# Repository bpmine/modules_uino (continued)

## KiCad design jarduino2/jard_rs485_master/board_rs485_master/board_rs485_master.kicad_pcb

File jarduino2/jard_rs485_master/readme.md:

# Maître des OYAsLe maître des OYAs permet de commander une pompe et plusieurs électrovannes pour remplir des OYAs.## OyasLes OYAs sont des sortes de pots en argile enterrés utilisés depuis des millénaires pour distribuer de l'eau à des cultures.On remplit régulièrement ces pots. Grâce à leur porosité, l'eau se diffuse à travers l'OYAs au fur et à mesure où les racines des plantes assèchent la terre à proximité.- Ils évitent les pertes d'eau par évaporation- ne mouillent pas les feuilles des plantes- ne mouille pas le sol en surface- évitent le stress hydrique- permettent de faire des économies d'eau## Description du système de remplissage automatiqueLe but du système de remplissage automatique des OYAs est de pouvoir s'absenter pendant les vacances tout en laissant les OYAs se gérer tous seuls.### Principe de fonctionnementDes cuves récupèrent l'eau de pluie. A partir de ces cuves, un système comportant une pompe et plusieurs électrovannes permet de remplir les OYAs.Le système rempli chaque OYA jusqu'au maximum ou bien selon le programme souhaité. La stratégie de remplissage est entièrement programmable.### CuvesNous avons 4 cuves pour une capacité totale d'environ 1600 L.- Cuve principale de 1000 L- cuve  "Paul" de 100 L (pour gouteurs petits bacs)- cuve "Réduit" de 250 L pour les OYAs- cuve "Barbec" de 250 L pour les OYAsDeux cuves de 250 L alimentent donc nos deux systèmes de remplissage automatique.Les cuves sont communicantes et un système permet de pomper l'eau de la cuve principale vers les autres. Ce système est décrit ici: [Modules Wifi IO](..\jard_wemos)Des modules Wifi permettent donc de piloter le remplissage des cuves.### Réseau/TuyauChaque système OYAs est composé d'un module maître et de plusieurs modules esclaves reliés entre eux par un réseau RS485 et un tuyau 12mm.Le câble réseau comporte une alimentation 12V et les fils A et B du RS485.Le réseau possède deux résistances de terminaison de 120 Ohms aux deux extrémités. Il est également polarisé côté maître par une pull up et une pull down de 220 Ohms (Valeur encore susceptible de bouger).Pour trouver les bonnes valeurs et étant donné la mauvaise qualité de câble utilisé, il faut effectuer des mesures de signal au bout du bus et vérifier que les tensions au repos de A et de B sont conformes à la norme RS485. __NB:__ Le dispositif de la photo ci-dessus contient une résistance de 128 Ohm. On appelle ça un "bouchon" !! (d'où le bouchon de liège...)## Modules électronique de pilotage### Module PompeLe module pompe contient une carte esclave RS485 en configuration "pompe".Connecteurs:- connecteur 4 voies bus RS485 + alim- connecteur pompe- connecteur débitmètreCe module est placé en sortie de cuve pour pomper l'eau et donner une certaine pression dans le tuyau. La pompe est nécessaire pour assurer un débit constant quelque soit le niveau d'eau dans la cuve et quelle que soit la hauteur relative entre la cuve et les différents OYAs.Il faut aussi noter qu'une pression minimale est nécessaire pour ouvrir une électrovanne (voir ces caractéristiques).Le schéma et le pcb de la carte sont ici: [Carte esclave RS485](..\jard_485_slave\board)Plusieurs versions ont été réalisées, compatibles entre-elles. A ce jour le système est composé de façon hétérogène par ces différentes versions.Version | Date | Description-- | -- | --Rev Ax | 2023 | Version initiale avec modules (forme en L)Rev Bx | 2023 | Correction RX/TX inverséRev Dx | 2024 | Version sans module (tout intégré en CMS)Rev Ex | 2024 | Avec modules (petite carte)Rev Gx | 2024 | MAX485 en CMS (petite carte)Le logiciel est ici: [Logiciel esclave RS485](..\jard_485_slave\soft)### Module OyaLe module OYA contient une carte esclave RS485 en configuration "OYA".Connecteurs:- connecteur 4 voies bus RS485 + alim- connecteur électrovanne- connecteur niveauxIl contient également une électrovanne 12V et un capteur de niveau.Ce module est placé sur chaque OYA.Le capteur de niveau comporte deux flotteurs qui ferment un contact en position basse.### Module Maître## Protocole réseau (RS485)### PrincipeLe réseau est de type RS485. Il comporte un maître et plusieurs esclaves. Chaque esclave a une adresse unique (de 1 à 14 ou 1 à E en hexadécimal).Seul le maître peut initier une communication. Un seul esclave peut répondre à une trame émise par le maître.Types de messages du maître:- Trame Commandes- Trame Ping- Trame SyncTypes de réponses d'un esclave:- Trame Pompe- Trame Oya- Trame PongLa communication se fait par cycles. Chaque cycle se termine par une trame Sync.Durant un cycle, le maître envoie autant de trames __*"Commandes"*__ qu'il y'a d'esclaves configurés. Chaque trame __*"Commandes"*__ comporte un appel destiné à un esclave en particulier. Seul l'esclave appelé peut répondre avec l'une des deux trames __*"Oya"*__ ou __*"Pompe"*__.Après un __*"Sync"*__, le maître doit impérativement attendre un temps minimum avant d'initier un nouveau cycle. Cela permet aux esclaves d'effectuer des traitements.#### Echange Commandes##### Trame Commandes##### Trame Pompe##### Trame Oya#### Echange Ping/Pong#### Timing notableTemps de cycleTemps entre le sync et un nouveau cycle

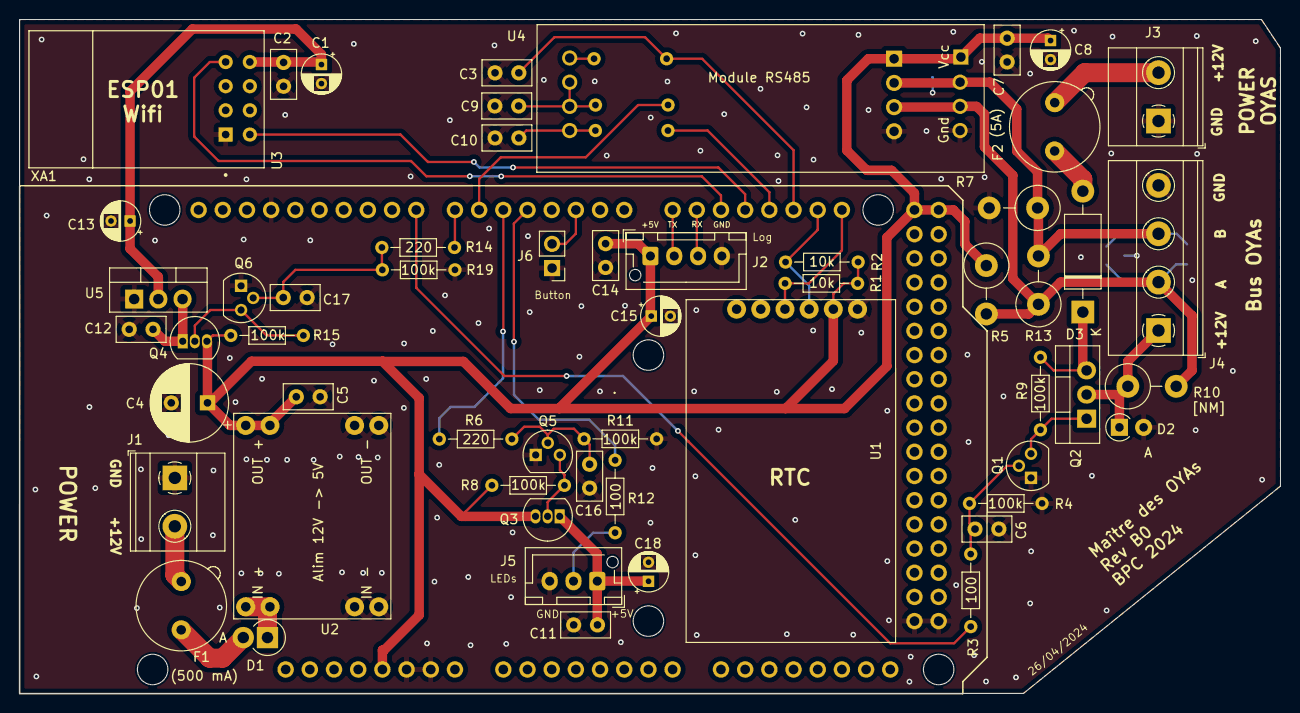
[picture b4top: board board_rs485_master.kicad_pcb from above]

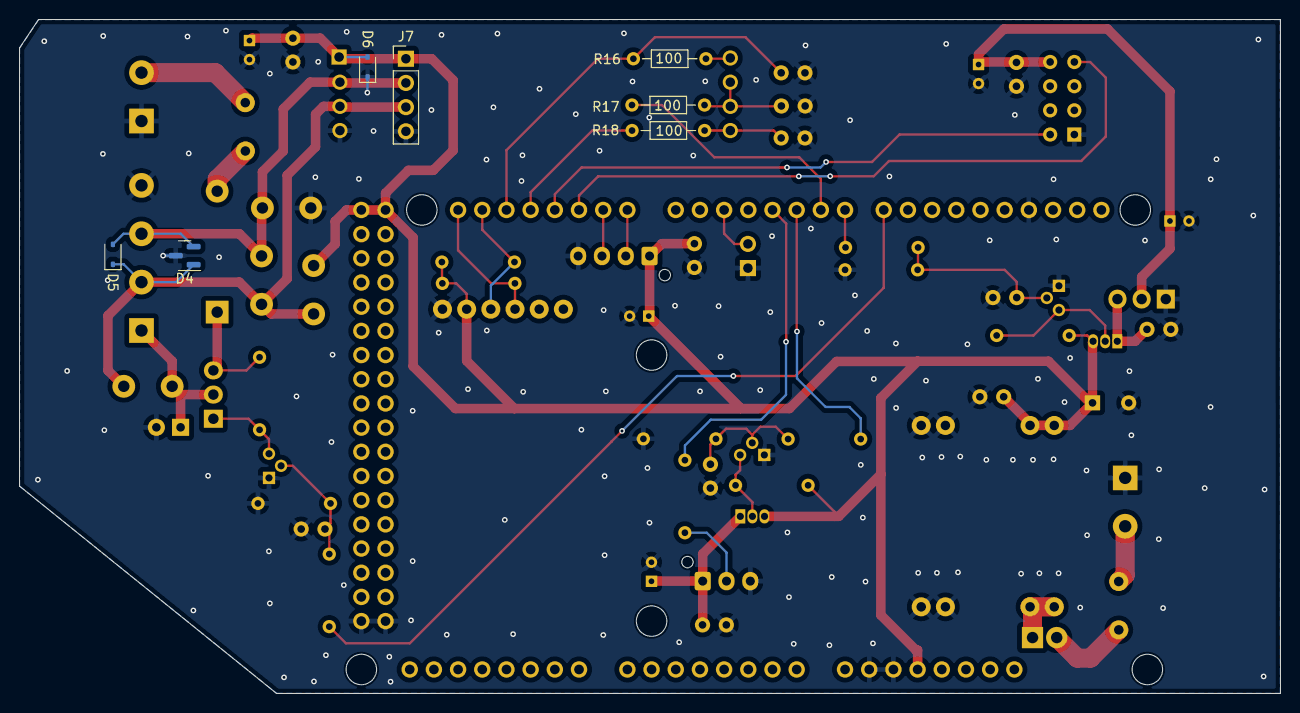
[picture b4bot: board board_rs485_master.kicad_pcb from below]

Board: 2 copper layers, 132.4 x 70.8 mm, 64 parts (7 on the bottom side), 38 nets.

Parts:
C1, C8, C13, C15, C18: 10µF; CP_Radial_D4.0mm_P2.00mm
C2, C5, C6, C7, C11, C12, C14, C16, C17: 100nF; C_Disc_D5.0mm_W2.5mm_P2.50mm
C3, C9, C10: 1nF; C_Disc_D5.0mm_W2.5mm_P2.50mm
C4: 100µF; CP_Radial_D8.0mm_P3.80mm
D1: SR560; D_DO-15_P2.54mm_Vertical_AnodeUp
D2: BAT42; D_A-405_P2.54mm_Vertical_AnodeUp
D3: SR560; D_DO-15_P12.70mm_Horizontal
D4: SM712_SOT23; SOT-23
D5, D6: SD12_SOD323; D_SOD-323
F1: 500 mA; Fuseholder_TR5_Littelfuse_No560_No460
F2: 5A; Fuseholder_TR5_Littelfuse_No560_No460
J1: POWER_12V; TerminalBlock_Phoenix_MKDS-1,5-2-5.08_1x02_P5.08mm_Horizont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
J2: Log; JST_XH_B4B-XH-AM_1x04_P2.50mm_Vertical
J3: POWER_OYAS_12V; TerminalBlock_Phoenix_MKDS-1,5-2-5.08_1x02_P5.08mm_Horizont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
J4: BUS_OYAS; TerminalBlock_Phoenix_MKDS-1,5-4-5.08_1x04_P5.08mm_Horizont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
J5: Leds RGB; JST_XH_B3B-XH-AM_1x03_P2.50mm_Vertical
J6: Button; PinHeader_1x02_P2.54mm_Vertical
J7: Adapt BUS; PinHeader_1x04_P2.54mm_Vertical
Q1, Q5, Q6: BPC_2N2222A; TO-92
Q2: P03P4L-04; TO-220-3_Vertical
Q3, Q4: BC327; TO-92_Inline
R1, R2: 10k; R_Axial_DIN0204_L3.6mm_D1.6mm_P7.62mm_Horizontal
R3, R12, R16, R17, R18: 100; R_Axial_DIN0204_L3.6mm_D1.6mm_P7.62mm_Horizontal
R4, R8, R9, R11, R15, R19: 100k; R_Axial_DIN0204_L3.6mm_D1.6mm_P7.62mm_Horizontal
R5, R7: 220; R_Axial_DIN0414_L11.9mm_D4.5mm_P5.08mm_Vertical
R6, R14: 220; R_Axial_DIN0204_L3.6mm_D1.6mm_P7.62mm_Horizontal
R10: R; R_Axial_DIN0414_L11.9mm_D4.5mm_P5.08mm_Vertical
R13: 128; R_Axial_DIN0414_L11.9mm_D4.5mm_P5.08mm_Vertical
U1: RtcArduino; BPC_RtcArduino
U2: BPC_Alim5V
U3: BPC_ESP8266-01_ESP-01; BPC_XCVR_ESP8266-01_ESP-01
U4: BPC_Mod485
U5: LM1117DT-3.3; TO-220-3_Vertical
XA1: Arduino_Mega2560_Shield; BPC_Arduino_Mega2560_Shield

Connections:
+5V: C4.1, C5.1, C7.1, C8.1, C14.1, C15.1, D6.2 (A2), J2.1, J7.1, Q3.3 (E), Q4.3 (E), R1.1, R2.1, R5.1, R8.1, R15.1, U1.2 (VCC), U2.7 (OUT+), U2.8 (OUT+), U4.1 (Vcc), XA1.5V1 (5V), XA1.5V3 (5V), XA1.5V4 (5V)
A: D4.1 (A1), D5.1 (A1), J4.2, J7.3, R5.2, R10.2, R13.1, U4.3 (A)
B: D4.2 (A2), D5.2 (A2), J4.3, J7.2, R7.1, R13.2, U4.2 (B)
CMD_LEDS_PWR: R6.1, XA1.D5
CMD_OYAS_PWR: R3.2, XA1.D8
CMD_WIFI_PWR: R14.1, XA1.D7
DATA_LEDS: R12.1, XA1.D4
GND: C1.2, C2.2, C3.2, C4.2, C5.2, C6.2, C7.2, C8.2, C9.2, C10.2, C11.2, C12.2, C13.2, C14.2, C15.2, C16.2, C17.2, C18.2, D2.2 (A), D4.3 (common), D6.1 (A1), J1.1, J2.4, J3.1, J4.4, J5.3, J6.1, J7.4, Q1.1, Q5.1, Q6.1, R4.2, R7.2, R11.2, R19.2, U1.1 (GND), U2.3 (IN-), U2.4 (IN-), U2.5 (OUT-), U2.6 (OUT-), U3.1 (GND), U4.4 (Gnd), U5.1 (GND), XA1.GND1 (GND), XA1.GND2 (GND), XA1.GND3 (GND), XA1.GND5 (GND), XA1.GND6 (GND)
unnamed: C6.1, Q1.2, R3.1, R4.1
unnamed: C16.1, Q5.2, R6.2, R11.1
unnamed: C17.1, Q6.2, R14.2, R19.1
unnamed: D1.2 (A), F1.1
unnamed: D1.1 (K), U2.1 (IN+), U2.2 (IN+)
unnamed: D2.1 (K), J4.1, Q2.2 (D), R10.1
unnamed: D3.2 (A), F2.1
unnamed: D3.1 (K), Q2.3 (S), R9.1
unnamed: F1.2, J1.2
unnamed: F2.2, J3.2
unnamed: C11.1, C18.1, J5.1, Q3.1 (C)
unnamed: J5.2, R12.2
unnamed: Q1.3, Q2.1 (G), R9.2
unnamed: Q3.2 (B), Q5.3, R8.2
unnamed: Q4.2 (B), Q6.3, R15.2
unnamed: C12.1, Q4.1 (C), U5.3 (VI)
unnamed: C9.1, R17.1, U4.6 (DE), U4.7 (RE)
unnamed: C10.1, R18.1, U4.5 (DI)
unnamed: R16.1, U4.8 (RO)
POWER_3.3: C1.1, C2.1, C13.1, U3.8 (VCC), U5.2 (VO)
RS485_RX: C3.1, R16.2, XA1.D19 (D19_RX1)
RS485_TX: R18.2, XA1.D18 (D18_TX1)
RX_LOG: J2.3, XA1.D15 (D15_RX3)
RX_WIFI: U3.5 (TXD), XA1.D17 (D17_RX2)
SCL: R1.2, U1.4 (SCL), XA1.D21 (D21_SCL)
SDA: R2.2, U1.3 (SDA), XA1.D20 (D20_SDA)
TEST_BTN: J6.2, XA1.D2 (D2_INT0)
TX_EN: R17.2, XA1.D6
TX_LOG: J2.2, XA1.D14 (D14_TX3)
TX_WIFI: U3.4 (RXD), XA1.D16 (D16_TX2)

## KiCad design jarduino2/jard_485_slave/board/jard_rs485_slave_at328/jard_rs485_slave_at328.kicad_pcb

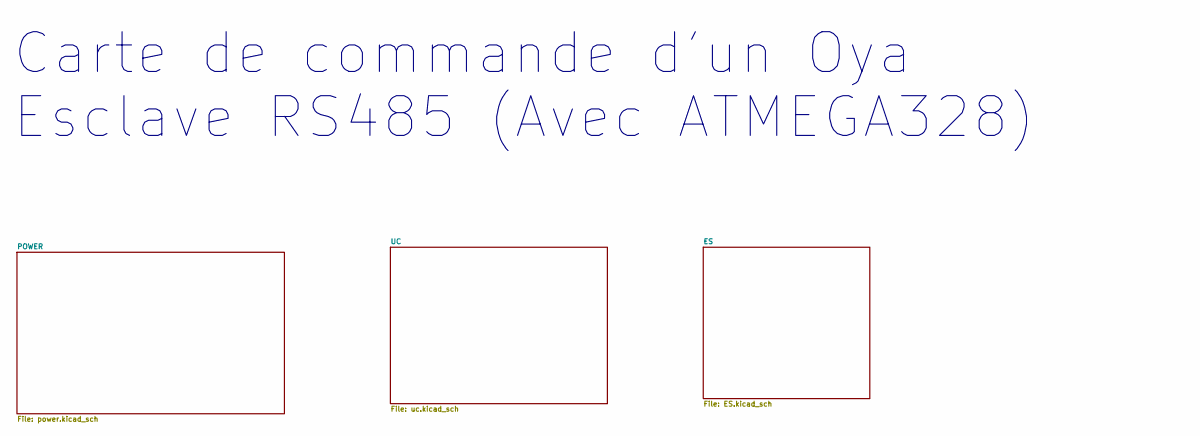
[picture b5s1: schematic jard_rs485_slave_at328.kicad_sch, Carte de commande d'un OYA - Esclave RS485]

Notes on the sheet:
Carte de commande d'un Oya Esclave RS485 (Avec ATMEGA328)

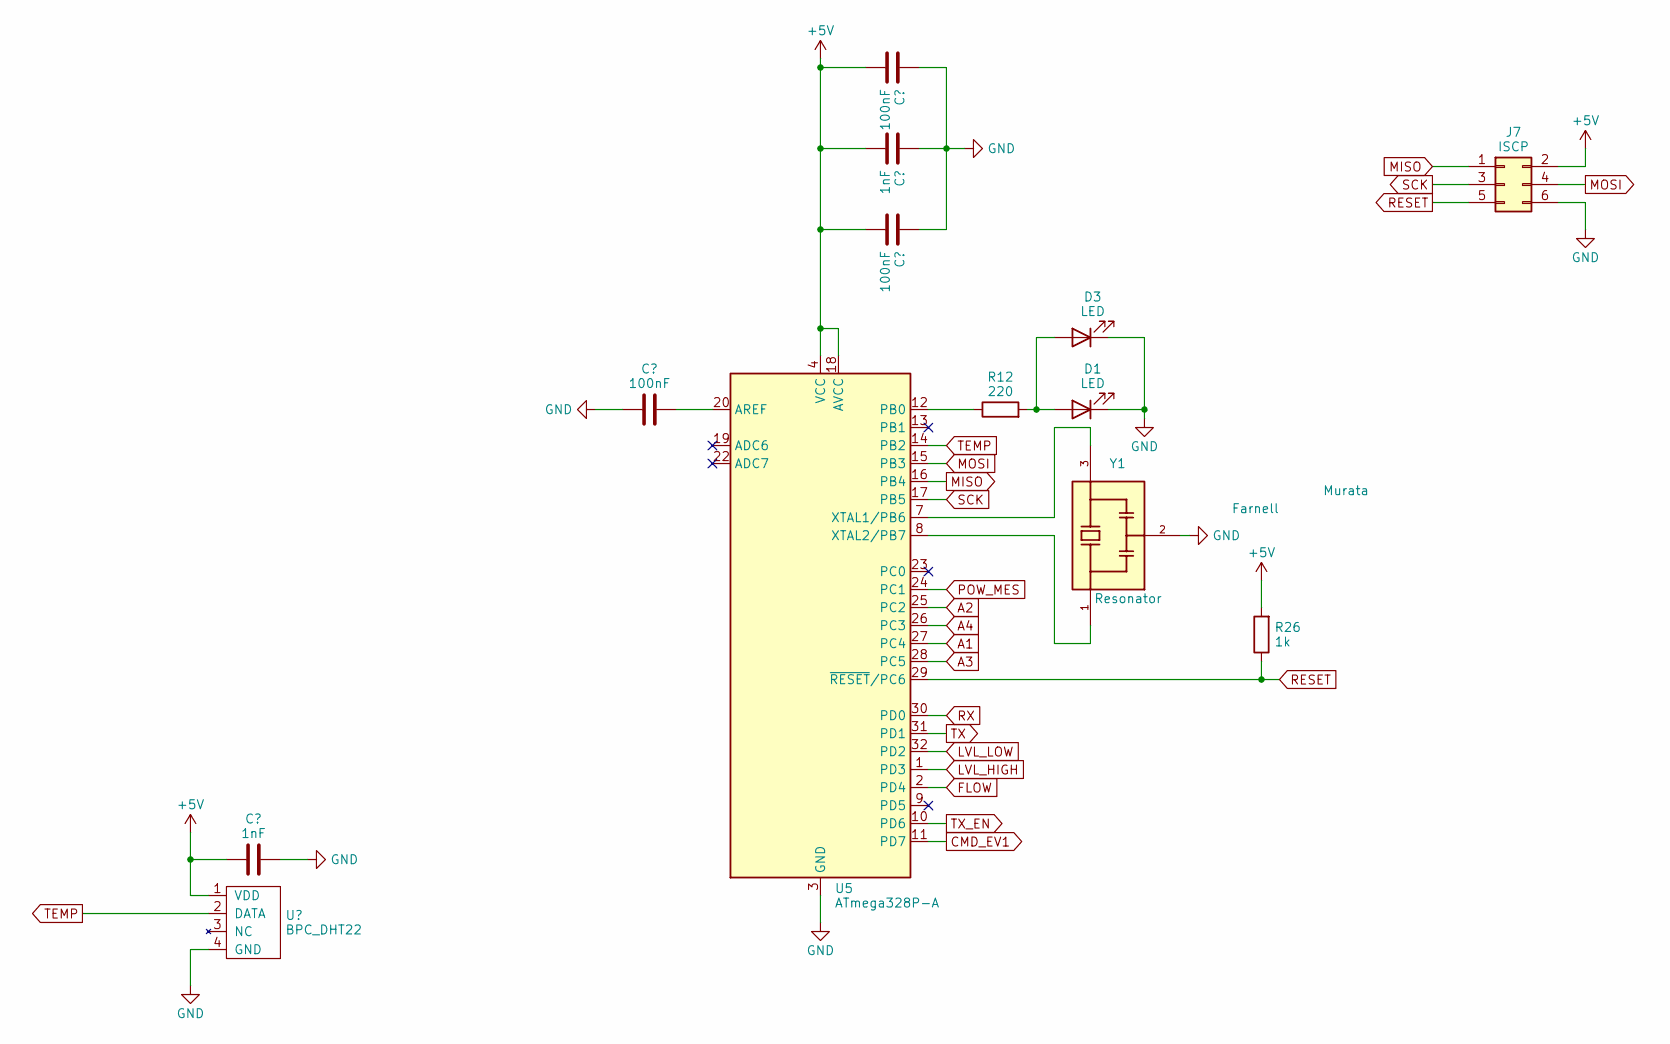
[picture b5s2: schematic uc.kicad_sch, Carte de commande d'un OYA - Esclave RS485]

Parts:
C5, C9, C13: 100nF; C_0603_1608Metric
C7, C8: 1nF; C_0603_1608Metric
D1: LED; LED_0805_2012Metric_Pad1.15x1.40mm_HandSolder
D3: LED; LED_D3.0mm_FlatTop
J7: ISCP; BPC_ISCP_CMS
R12: 220; R_0805_2012Metric_Pad1.20x1.40mm_HandSolder
R26: 1k; R_0805_2012Metric_Pad1.20x1.40mm_HandSolder
U5: ATmega328P-A; TQFP-32_7x7mm_P0.8mm
U6: BPC_DHT22
Y1: Resonator; BPC_16MHz_CSTNE16M0V530000R0; PARTREV JGC42-8853B

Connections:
+5V: C5.2, C7.1, C8.2, C9.2, J7.2 (VCC), R26.2, U5.4 (VCC), U5.6 (VCC), U5.18 (AVCC), U6.1 (VDD); also elsewhere on the board
A1: U5.27 (PC4); also elsewhere on the board
A2: U5.25 (PC2); also elsewhere on the board
A3: U5.28 (PC5); also elsewhere on the board
A4: U5.26 (PC3); also elsewhere on the board
CMD_EV1: U5.11 (PD7); also elsewhere on the board
FLOW: U5.2 (PD4); also elsewhere on the board
GND: C5.1, C7.2, C8.1, C9.1, C13.1, D1.1 (K), D3.1 (K), J7.6 (GND), U5.3 (GND), U5.5 (GND), U5.21 (GND), U6.4 (GND), Y1.2; also elsewhere on the board
LVL_HIGH: U5.1 (PD3); also elsewhere on the board
LVL_LOW: U5.32 (PD2); also elsewhere on the board
MISO: J7.1 (MISO), U5.16 (PB4)
MOSI: J7.4 (MOSI), U5.15 (PB3)
unnamed: D1.2 (A), D3.2 (A), R12.2
unnamed: C13.2, U5.20 (AREF)
unnamed: R12.1, U5.12 (PB0)
unnamed: U5.7 (XTAL1/PB6), Y1.3
unnamed: U5.8 (XTAL2/PB7), Y1.1
POW_MES: U5.24 (PC1); also elsewhere on the board
RESET: J7.5 (RST), R26.1, U5.29 (~RESET/PC6)
RX: U5.30 (PD0); also elsewhere on the board
SCK: J7.3 (SCK), U5.17 (PB5)
TEMP: U5.14 (PB2), U6.2 (DATA)
TX: U5.31 (PD1); also elsewhere on the board
TX_EN: U5.10 (PD6); also elsewhere on the board

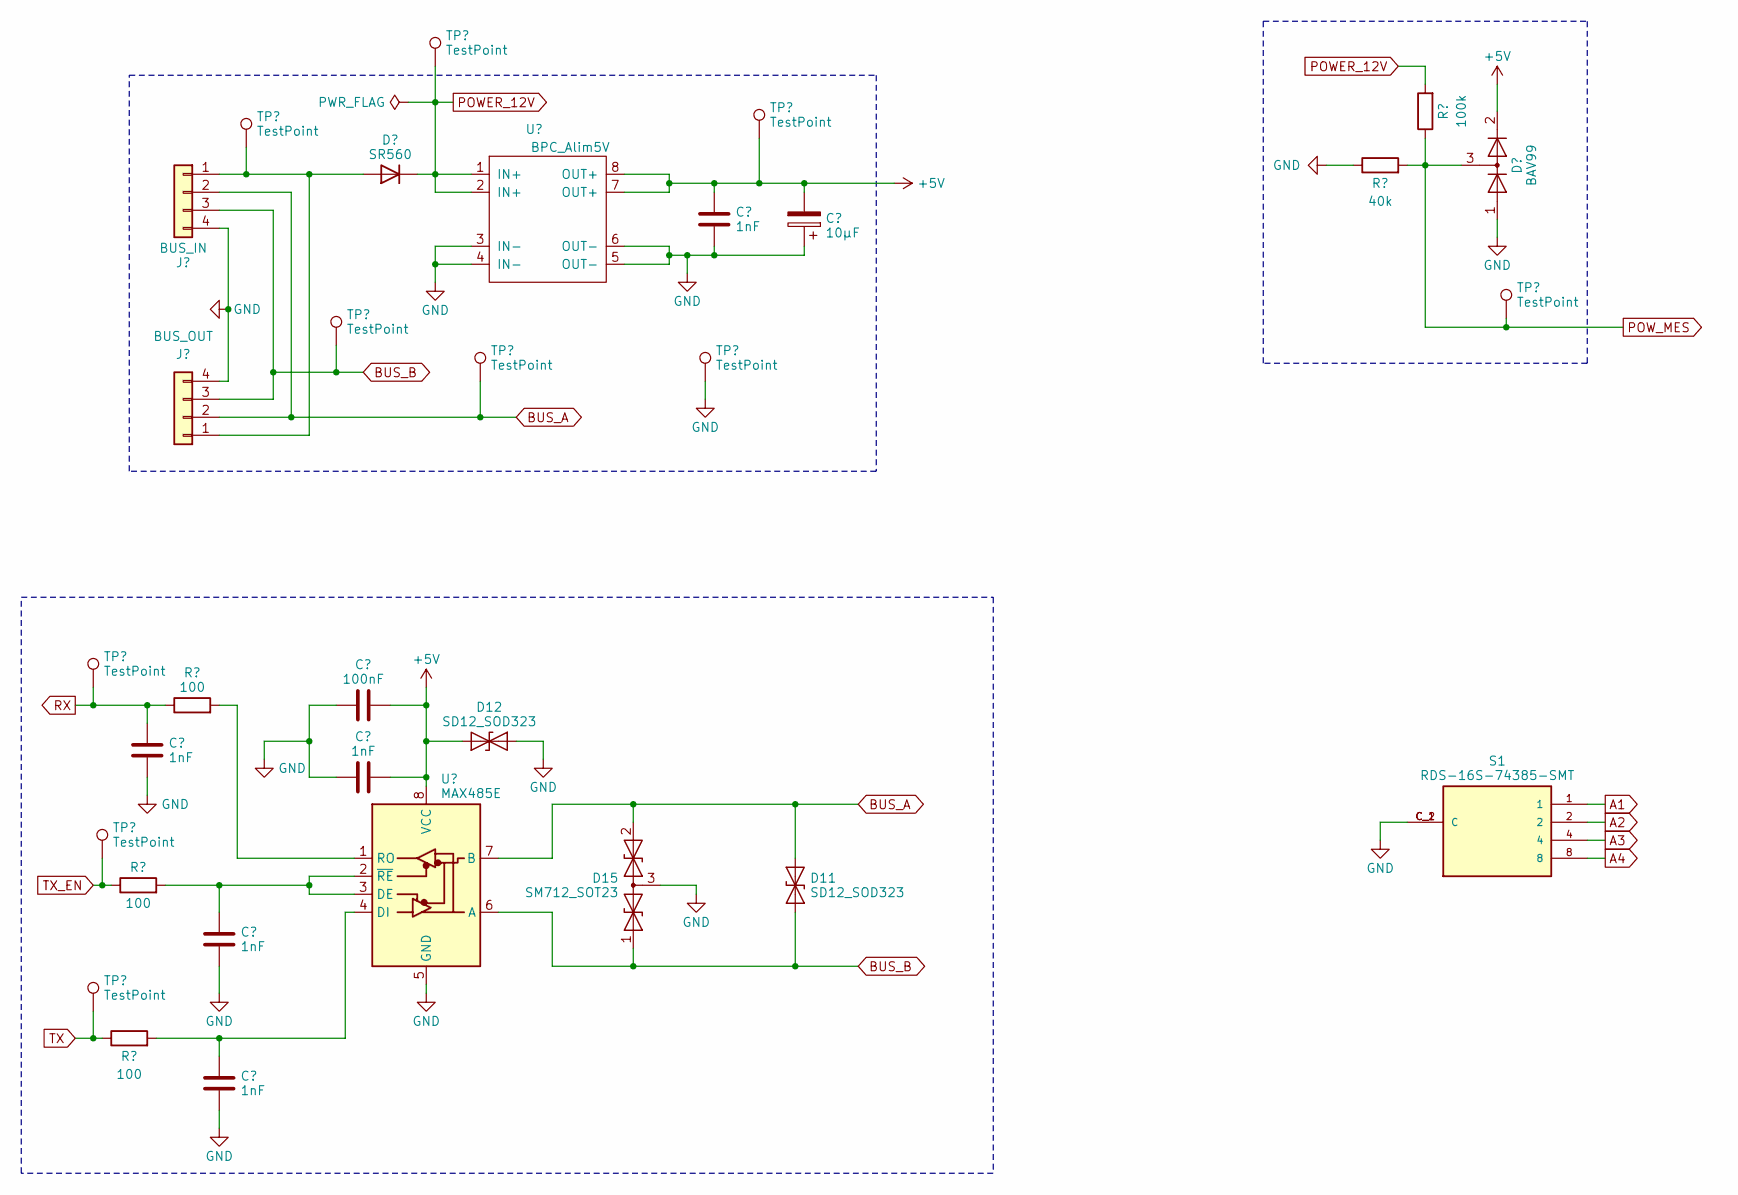
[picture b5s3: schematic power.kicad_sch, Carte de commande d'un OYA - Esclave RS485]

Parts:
C1, C4, C10, C11, C12: 1nF; C_0603_1608Metric
C2: 10µF; CP_Elec_5x5.9
C3: 100nF; C_0603_1608Metric
D2: SR560; D_A-405_P7.62mm_Horizontal
D5: BAV99; SOT-23
D11, D12: SD12_SOD323; D_SOD-323
D15: SM712_SOT23; SOT-23
J1: BUS_IN; TerminalBlock_Phoenix_MPT-0,5-4-2.54_1x04_P2.54mm_Horizontal
J2: BUS_OUT; TerminalBlock_Phoenix_MPT-0,5-4-2.54_1x04_P2.54mm_Horizontal
R1, R2, R3: 100; R_0805_2012Metric_Pad1.20x1.40mm_HandSolder
R4: 40k; R_0805_2012Metric_Pad1.20x1.40mm_HandSolder
R5: 100k; R_0805_2012Metric_Pad1.20x1.40mm_HandSolder
S1: RDS-16S-74385-SMT; BPC_RDS-16S-74385-SMT; PARTREV 1.0
TP1, TP2, TP3, TP4, TP5, TP6, TP7, TP8, TP9, TP10: TestPoint; TestPoint_Pad_D1.5mm
U1: BPC_Alim5V
U2: MAX485E; SO-8_3.9x4.9mm_P1.27mm

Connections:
+5V: C1.1, C2.2, C3.1, C4.1, D5.2 (A), D12.2 (A2), TP8.1, U1.7 (OUT+), U1.8 (OUT+), U2.8 (VCC); also elsewhere on the board
A1: S1.1; also elsewhere on the board
A2: S1.2; also elsewhere on the board
A3: S1.4; also elsewhere on the board
A4: S1.8; also elsewhere on the board
BUS_A: D11.2 (A2), D15.2 (A2), J1.2, J2.2, TP6.1, U2.7 (B)
BUS_B: D11.1 (A1), D15.1 (A1), J1.3, J2.3, TP3.1, U2.6 (A)
GND: C1.2, C2.1, C3.2, C4.2, C10.2, C11.2, C12.2, D5.1 (K), D12.1 (A1), D15.3 (common), J1.4, J2.4, R4.1, S1.C_1 (C), S1.C_2 (C), TP10.1, U1.3 (IN-), U1.4 (IN-), U1.5 (OUT-), U1.6 (OUT-), U2.5 (GND); also elsewhere on the board
unnamed: D2.2 (A), J1.1, J2.1, TP2.1
unnamed: C11.1, R1.2, U2.2 (~RE), U2.3 (DE)
unnamed: C12.1, R3.2, U2.4 (DI)
unnamed: R2.2, U2.1 (RO)
POWER_12V: D2.1 (K), R5.2, TP5.1, U1.1 (IN+), U1.2 (IN+); also elsewhere on the board
POW_MES: D5.3 (K), R4.2, R5.1, TP9.1; also elsewhere on the board
RX: C10.1, R2.1, TP1.1; also elsewhere on the board
TX: R3.1, TP7.1; also elsewhere on the board
TX_EN: R1.1, TP4.1; also elsewhere on the board

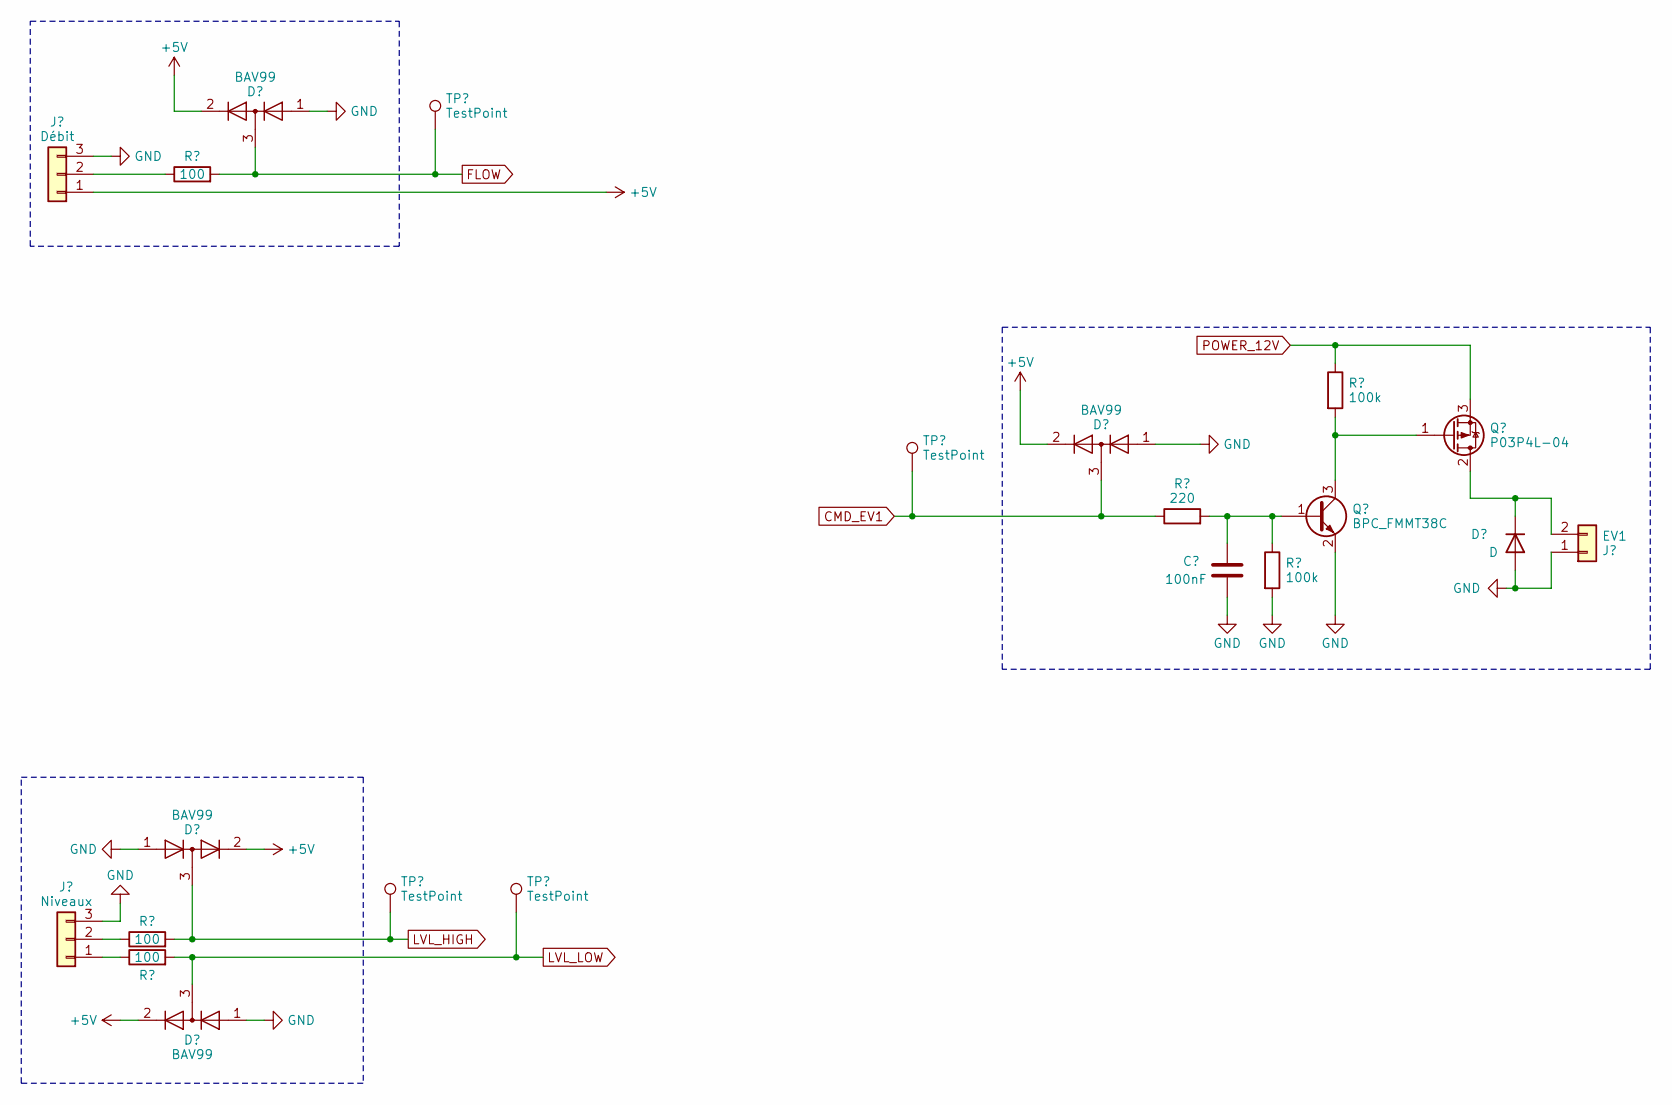
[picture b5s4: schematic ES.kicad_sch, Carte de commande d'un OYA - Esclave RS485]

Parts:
C6: 100nF; C_0603_1608Metric
D6, D7, D8, D10: BAV99; SOT-23
D13: D; D_A-405_P5.08mm_Vertical_KathodeUp
J3: Débit; TerminalBlock_Phoenix_MPT-0,5-3-2.54_1x03_P2.54mm_Horizontal
J4: Niveaux; TerminalBlock_Phoenix_MPT-0,5-3-2.54_1x03_P2.54mm_Horizontal
J6: EV1; TerminalBlock_Phoenix_MPT-0,5-2-2.54_1x02_P2.54mm_Horizontal
Q4: BPC_FMMT38C; BPC_SOT-23-3
Q6: P03P4L-04; TO-220-3_Vertical
R7, R8, R9: 100; R_0805_2012Metric_Pad1.20x1.40mm_HandSolder
R13: 220; R_0805_2012Metric_Pad1.20x1.40mm_HandSolder
R15, R17: 100k; R_0805_2012Metric_Pad1.20x1.40mm_HandSolder
TP11, TP12, TP13, TP15: TestPoint; TestPoint_Pad_D1.5mm

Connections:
+5V: D6.2 (A), D7.2 (A), D8.2 (A), D10.2 (A), J3.1; also elsewhere on the board
CMD_EV1: D10.3 (K), R13.1, TP15.1; also elsewhere on the board
FLOW: D8.3 (K), R7.2, TP11.1; also elsewhere on the board
GND: C6.2, D6.1 (K), D7.1 (K), D8.1 (K), D10.1 (K), D13.2 (A), J3.3, J4.3, J6.1, Q4.2 (E), R15.2; also elsewhere on the board
LVL_HIGH: D6.3 (K), R8.2, TP12.1; also elsewhere on the board
LVL_LOW: D7.3 (K), R9.2, TP13.1; also elsewhere on the board
unnamed: D13.1 (K), J6.2, Q6.2 (D)
unnamed: J3.2, R7.1
unnamed: J4.1, R9.1
unnamed: J4.2, R8.1
unnamed: C6.1, Q4.1 (B), R13.2, R15.1
unnamed: Q4.3 (C), Q6.1 (G), R17.2
POWER_12V: Q6.3 (S), R17.1; also elsewhere on the board

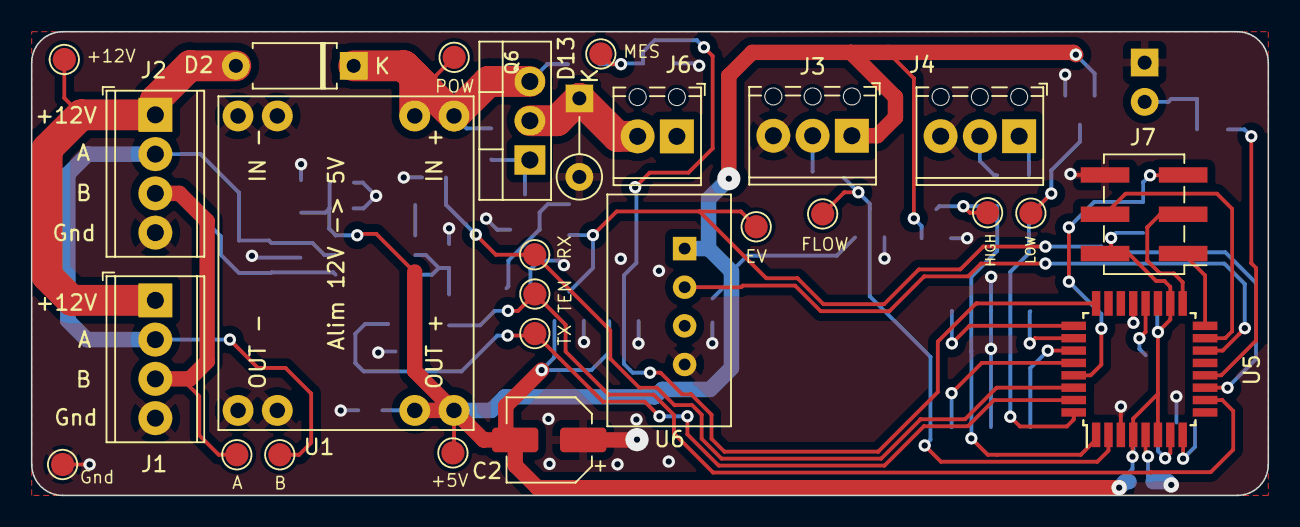
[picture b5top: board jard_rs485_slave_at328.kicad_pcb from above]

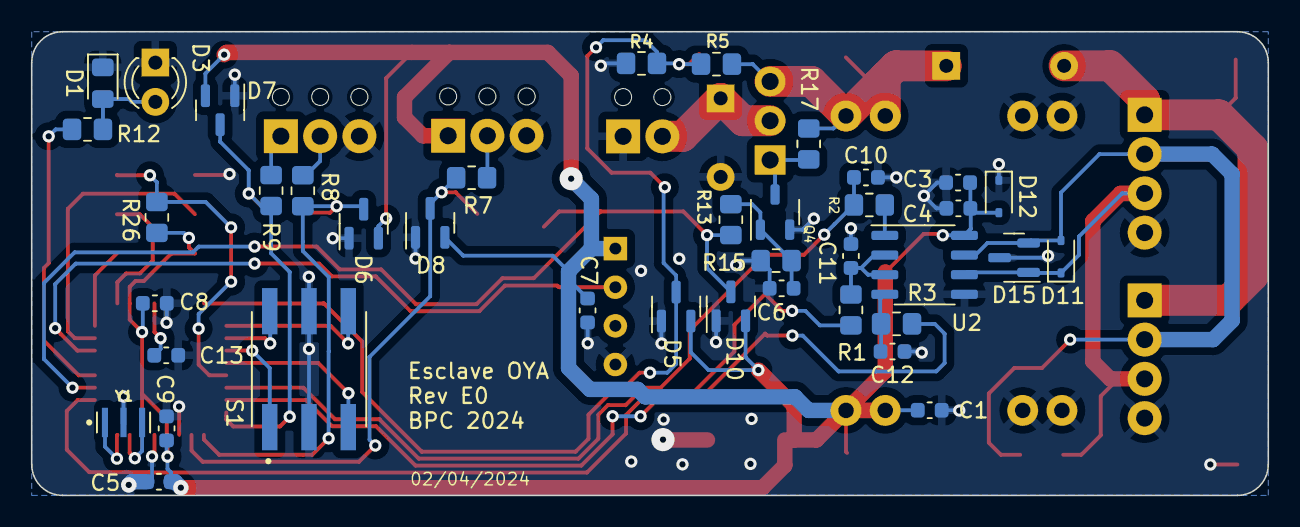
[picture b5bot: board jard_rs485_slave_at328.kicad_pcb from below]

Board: 2 copper layers, 80.0 x 30.0 mm, 66 parts (39 on the bottom side), 37 nets.

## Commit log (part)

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2021-02-05 Lecteur de badge arduino avec sa lib python
2021-02-07 Ajout images + schéma
2021-02-24 Schema de sonnette envoyé aujourd'hui pour tester Fritzing
2021-03-06 Finalisation programme - Envoi messages sur rabbit - Detection mouvement - Sonnette - Visu sonné ou bougé - Mode silencieux
2021-03-09 Tentative amélioration suite panne de reseau: - Si pas de wifi - ou pas de MQTT
    On fonctionne quand meme et on retente en tache de fond.
    Il reste un temps mort pendant la tentative MQTT ou on ne detecte pas l'appui.
2021-03-09 Debug avec changement d'IP du rabbit + flag retain pour conserver le msg
2021-03-09 Changement de lib MQTT pour https://github.com/arduino-libraries/ArduinoMqttClient
    Marche en QoS 1 => Messages persistants !
2021-03-24 Pour relevé temperature/humidité
2021-03-26 Creation jarduino 2
    - Une carte de commande à base de MSP 430 (A valider / revoir pnp cmd / alim 3.3 v)
    - Une carte IHM à LEDs
2021-03-28 Modif texte et resultats
2021-03-28 Depouillement
2021-03-28 Meuble
2021-04-13 Amélioration proto: - Diametre trous de fixation 4mm (avec compo sepcial) - SW1/SW2 echanges Batt/Sol
2021-05-20 Bouchon 4 : - Pas de vis aux normes - Aggrandissement de l'embout - Aggrandissement des trous du filtre
2021-05-24 Schéma jarduino2 avec nano: - RTC - 2 pompes - Borniers au lieu des connecteurs - composants traversants
    Composants trouvés lors de la réalisation du schéma précédent (jarduino2)
    Programme ino avec nano: MAQUETTE jarduino2.ino:
    - Lipo 3S comme batterie
    - BMS
    - Chargeur Mppt
    - DC DC 5V
2021-06-12 cleanup
2021-06-12 Ajout des autres types de message (msg, stats, cmds) Amélioration en cas d'erreurs
2021-06-27 Ajout second jarduino
2022-03-19 Ajout capteur de temp et hum + ext serie
2022-05-15 Premiers tests au jardin
2022-06-10 Intégration de la lib msbus
    Gestion de quelques objets MODBUS pour les tests
2022-06-13 Version programmée dans les jarduino aujourd'hui (Version 1)
2022-06-18 Deplacement des fichiers du namo a part
    Ajout du script python pour configurer le jarduino
2022-07-17 Amélioration suite modif reglages 1 et 3
2022-07-20 jard_nano: Ajout du mode veille et diverses améliorations
    - Ajout du mode veille (Extinction des LEDs si inactif, reveil avec boutons)
    - Ajout infos tensions/veille sur modbus
    - Port à 115200 (compatibilité time out modbus)
    - Gestion durées à cheval su 00:00
2022-07-20 JardConfig: Ajout Fermeture sur bouton Quit
2022-07-21 jard_nano: Remontée de bits manquant par MODBUS (veille, batt, ...) JardConfig: Ajout du monitoring
2022-07-21 Gestion pompage à cheval sur minuit
2022-07-24 jard_wifi: Creation du maître Modbus / Wifi avec ESP
    - Realisation du cycle de lecture (Coils + mesures communes, ...)
    - Ecriture d'une coil
    - Programmes de test (et du test du programme de test !)
2022-08-02 Oubli...
2022-08-23 Ajout d'un serveur web par Wifi:
    - /test pour tester
    - /info pour récupérer les infos du jarduino
2022-09-10 Preparation modèle 2023
    - Plus de hauteur sur pas de vis
    - 2 trous de plus sur le côté
    - Diamètre inférieurs à l'intérieur du tuyau
2022-09-10 Erreur unité des timers veille et comm
2022-09-11 Oubli source du pressostat
2022-09-11 Version testée rapidement avec nano: Fonctionne ok mais consomme beaucoup trop !!
2022-10-08 Log toutes les minutes + log VCC et Batt + validation valeurs
2022-10-08 Finalisation / mesure Vbatt / ...
2022-11-05 Réalisation d'un embout à coller
2022-11-26 Creation du logiciel client RS485
    Ce programme est un client modbus
    - Read/write coil 0 = Commande EV
    - Read inputs 0 et 1 = Capteur Niveau bas et haut
    - Write Register 0 = Change l'adresse modbus
2023-02-03 Ajout submodule
2023-02-06 Tout pret et testé niveau 458
2023-02-10 Docs
2023-02-21 Erreur marquage fusible
2023-03-02 Ajout d'une carte CMS générique: Commande pompes et EVs
2023-03-05 Ajustement sérigraphie
2023-03-07 Création maître OYA RS485
    - 1 Bus RS485 (Résistance configurable)
    - 1 Module Wemos (+ extension RTX SD possible)
    - 1 EEPROM 1k
    - 1 Sortie 12V/5A pilotable
    - 1 Alim DC/DC 5V
2023-03-23 Autre méthode pour filtrer (dans le réservoir)
    Filtre moins fin
2023-03-25 Correction épaisseur cyclindre pas de vis
2023-03-27 Finalisation carte Wifi I/O
2023-04-22 Version qui fonctionne ce jour avec les cuves
2023-05-06 Tel que testé cette aprem avec 3 Wifi IOs
2023-05-07 test_simple_prot.py
2023-05-08 Agrandir sérigraphie connecteurs bus Correction erreur inversion sérigraphie 1 et 4 sur J2 Correction inversion RX/TX sur module RS485 Inversion sérigraphie Niveaux/Débit
2023-05-08 Préparation jarduino slave RS485 Rev B0
2023-05-08 Changement alim 5V -> 3.3V
2023-05-09 WS pour piloter les Wifi IO
    /states retourne l'état des modules et des remplissages (voir code)
    /rempli/<name>?on=1 active le remplissage <name>
    /rempli/<name>?limit_src=3 Arret du remplissage quand le niveau 3 est perdu sur la source
    /rempli/<name>?cons_tgt=2 Arret du remplissage quand le niveau 2 est atteint sur la destination
2023-05-20 Test avec 1 pompe et 2 oyas
2023-05-21 Formatage
2023-06-18 Creation du maître 485 avec ATMEGA 2560
2023-06-19 Création carte maître RS485
2023-06-24 Consultation etat des oyas + diverses cmds term
2023-06-30 Debug et premier test avec terminal ok
    - Active désactive le maître
    - Pilote les oyas
2023-07-01 Rework machine à état et fin du codage (dont mode sleep)
2023-07-07 Mise au point et test ce soir
    Plus d'erreurs avec bus correctement polarisé
    Ajout de stats d'erreurs
    Ajout Oya F
2023-07-08 Import avec eclipse pour plus de facilité Codage filtrage bouton test (Voir btn.hpp) Permier test complet RTC + Test.
2023-07-10 Creation d'un service MQTT/Redis de gestion des Wifi IO
2023-07-14 Mise au point finale
    - Defines importants en haut du fichier
    - Tempo de mise en veille (+ temps d'envoyer un dernier message)
    - Ajout rssi, tick et pwr dans les datas
    - Gestion commande sleep et ping
    - Cas d'attente première réponse après boot
    Utilisation intensive cette après-midi
2023-07-14 Tel qu'utilisé lors du remplissage ce soir
2023-07-16 Timeout de remplissage Diverses amélioration MAIS dégradation du réseau à cause des logs .....
2023-07-16 Ajout on/off
2023-07-17 Suite aux tests aujourd'hui.
2023-07-18 Juste un client pour superviser les reservoirs
2023-07-18 Mode veille + finitions
2023-08-06 Tel qu'utilisé pendant les vacances
2023-08-20 Ajout du service de remplissage auto
2023-08-24 Correction remplissage de Paul
2023-09-03 Installation sur orange pi
2023-09-24 Création maître des oyas
2023-09-25 Création esclave Oyas avec MSP430
2023-10-07 Après nettoyage et vérification des règles
2023-12-23 Création du nouveau logiciel:
    - semuino_test: Logiciel pour tester la carte
    - semuino: Logiciel nano autonome
    - semuino_nano_slave: La nano est esclave (du ESP01)
    - semuino_nano_master_test: Un maitre nano pour tester l'esclave
2023-12-24 Description programmes
2023-12-24 Description WS (suite) + description espace mémoire I²C
2024-01-15 Ajout d'un warning sur le schéma pour indiquer que l'alimentation 5V doit être filtrée pour éviter les perturbations.
    Sinon les RGBs ne fonctionnent pas
    Plus tard, cette capa pourrait être intégrée à la carte ?
2024-01-20 Finalisattion du montage et tests
    Alim 5V KO => Utilisation alim extérieure 230V/5V/10A
2024-01-27 Mise au point pour essais
    + photos et description meuble 2024
2024-01-28 Plage finale: de 6h00 à 22h00
2024-03-08 Nouvel algo + marquage V1.0
    - On monte en blanc avec les RGB seules de 6h à 7h (de 0 à 1000 LUX)
    - On allume les 12V + RGB en rouge horticole de 7h à 12h (1600 LUX)
    - On allume les 12V + RGB en blanc de 12h a 14h (2000 LUX)
    - On revient à 12V + RGB rouge de 14h à 21h (1600 LUX)
    - On descend en blanc avec les RGB seules de 21h à 22h (de 1000 LUX à 0)
2024-03-08 Mise à jour suite aux mesures d'éclairage
2024-03-14 Ajout de précisions sur le WS et le protocole I²C
2024-03-16 Report et adaptation du code du semuino autonome Manque la partie config et LED
2024-03-16 Complément de description
2024-03-16 Mise au point et commentaires
2024-03-17 Ajout de doxygen
2024-03-17 Passage à Kicad V7.0 Ajout de switches pour l'adresse de l'esclave
2024-03-24 Nouvel essai de routage avec en + LEDs
2024-03-26 Le maître des oyas devient un shield ATMEGA
    - RTC
    - ESP
    - LEDs RGB
    - Alim 5V
    - RS485
    - Alim 12V commutée
2024-03-29 Fin du routage. Prêt pour revue.
2024-03-30 Candidate pour revue du master Oyas (avec modules en tant que shield MEGA)
2024-03-31 Finalisation dossier
2024-04-01 Correction empreinte résonateur
2024-04-02 Correction erreur de MOS (N au lieu de P) + Saisie complete de la BOM
2024-04-06 Ajout des prix des composants
2024-04-09 Amélioration suite remise en route:
    - Agrandissement trous des LEDs D1 et D3
    - Correction erreur type du MOS P GDS
    - Agrandissement empreintes de R5,R7,R13 et R10 + verticales
    - Ajout de la description des opérations de rework pour le MOD485
    - Ajout d'une interface pour adapter le bus (5V, A, B et Gnd)
2024-04-14 Finitions avant envoi
2024-04-24 Déplacer C13 pour éviter le contact avec le port USB de la MEGA2460
2024-04-24 Création du programme de test fabrication ok
2024-04-25 Correction de l'inversion RX/TX du module Wifi
2024-04-26 Changement de la logique de commande des PWR Wifi et LEDs (avec un npn en plus)
2024-04-27 Déplacement piste LED car trop proche du bord
2024-05-01 Relier RST et D0 pour la sortie de veille (strap sur A0 et B0)
2024-05-01 Filtrage acquisition analogique et conversion échelle dixième de volts (120 = 12 V)
2024-05-03 Fin de codage esclave + début des tests
2024-05-04 Inversion RX/TX 485
2024-05-05 Suppression du module RS485 et remplacement par le CI MAX485E lui-même. Preparation version G...
2024-05-06 Réaffactation des commandes PWR de Wifi et LEDs (compatibilité soft) + suppression de la sheet Wifi sur le schéma (regreoupé dans UC)
2024-05-14 Amélioration programmation adresse et timers de timeout Ajout de la commande de RAZ du temps total en s
    - Clignote lentement (1s) = Adresse non initialisee
    - Clignote brièvement toutes les secondes = Programme init en cours (il faut mettre un prog normal)
    - Clignote rapidement (200ms) = sortie activee
    - Clignote plus lentement (500ms) = pas de sync donc pas de remonte de datas vers le maitre
    - Fixe = Reseau ok (cmd + sync)
    - Eteint = Pas de reseau
2024-05-17 Agrandissement pastilles Mod RS485
2024-05-18 Il faut les pullup internes pour la Rev Ex
2024-05-19 Finalisation Comm wifi avec etat des commandes distantes Creation machine à états de gestion de l'appli (manager)
2024-05-19 Codage wifi (suite)
2024-05-20 Fin test du jour avec pilotage des oyas à distance
2024-05-26 Readme systeme OYAs
2024-05-26 Description Pompe et Oya
2024-06-02 Mise au point esclave (probleme d'instabilite car depassement de pile)
2024-06-08 Ajustement tmt de sync à 6 s (time cmd a 4s)
2024-06-08 Re-programmation de tous les premiers Oyas @1 à @8 (et passage au Nano 328)
2024-06-09 Mise au point avec les oyas du reduit +Ajout du mode display par appui sur test
2024-06-10 Retouche avant envoi
2024-06-16 Amélioration test esclave
2024-06-16 Amelioration tests+...
2024-06-27 Note à faire
2024-07-04 Integration de la lib mdbus directement dans les sources du jarduino
2024-07-04 - Ajout fonctions Raz et Ping - Timeout reset et plein retouches et differentiation petits OYAs - Mode recherche Wifi avec LED jaune (non testé: A finaliser) - Prise en charge mecanisme de commandes 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
2024-07-07 Ajustement apres mesure @8 et @9 sur reduit
2024-07-14 Ajustement Reduit (moins de temps de remplissage)
2024-07-17 Marche toujours pas (master.loop a virer)
2024-07-18 Mise au point Wifi: Communique en montant
2024-07-19 Integration avec le serveur et dernieres mises au point
2024-08-24 Suppression fichiers copies vers le nouveau repo Jarduino
2024-09-28 Ajout tel qu'utilisé cet été
2024-09-28 Déplacement vers autre repo Jarduino
